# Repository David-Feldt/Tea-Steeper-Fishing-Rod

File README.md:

# Tea steeping robot

I found myself forggetting to take my tea bag and how long its been in the water. This robot you set a timer and it will remove the tea bag to your desired time.
- Built using esp8266 devboard and esp8266 (based on freeRTOS)
- PCB was made in KiCad
- Mechanical is built with scrap material

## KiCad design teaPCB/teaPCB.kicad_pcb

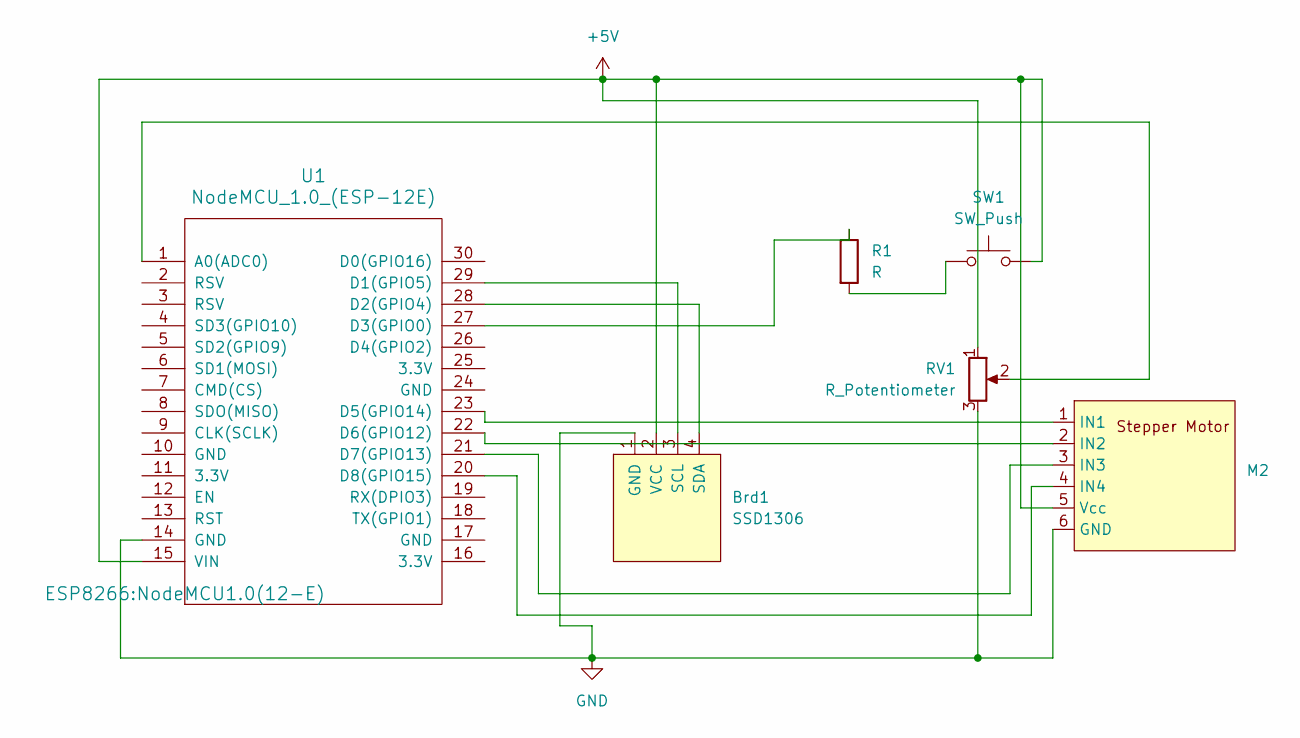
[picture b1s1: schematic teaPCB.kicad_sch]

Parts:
Brd1: SSD1306; 128x64OLED
M2: stepper motor
R1: R; R_Axial_DIN0207_L6.3mm_D2.5mm_P10.16mm_Horizontal
RV1: R_Potentiometer; Potentiometer_Alps_RK09Y11_Single_Horizontal
SW1: SW_Push; SW_Push_2P1T_Toggle_CK_PVA1xxH1xxxxxxV2
U1: NodeMCU_1.0_(ESP-12E); NodeMCU1.0(12-E)

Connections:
+5V: Brd1.2 (VCC), M2.5 (Vcc), RV1.1, SW1.2, U1.15 (VIN)
GND: Brd1.1 (GND), M2.6 (GND), RV1.3, U1.14 (GND)
unnamed: Brd1.3 (SCL), U1.29 (D1(GPIO5))
unnamed: Brd1.4 (SDA), U1.28 (D2(GPIO4))
unnamed: M2.1 (IN1), U1.23 (D5(GPIO14))
unnamed: M2.2 (IN2), U1.22 (D6(GPIO12))
unnamed: M2.3 (IN3), U1.21 (D7(GPIO13))
unnamed: M2.4 (IN4), U1.20 (D8(GPIO15))
unnamed: R1.2, SW1.1
unnamed: RV1.2, U1.1 (A0(ADC0))
unnamed: R1.1, U1.27 (D3(GPIO0))

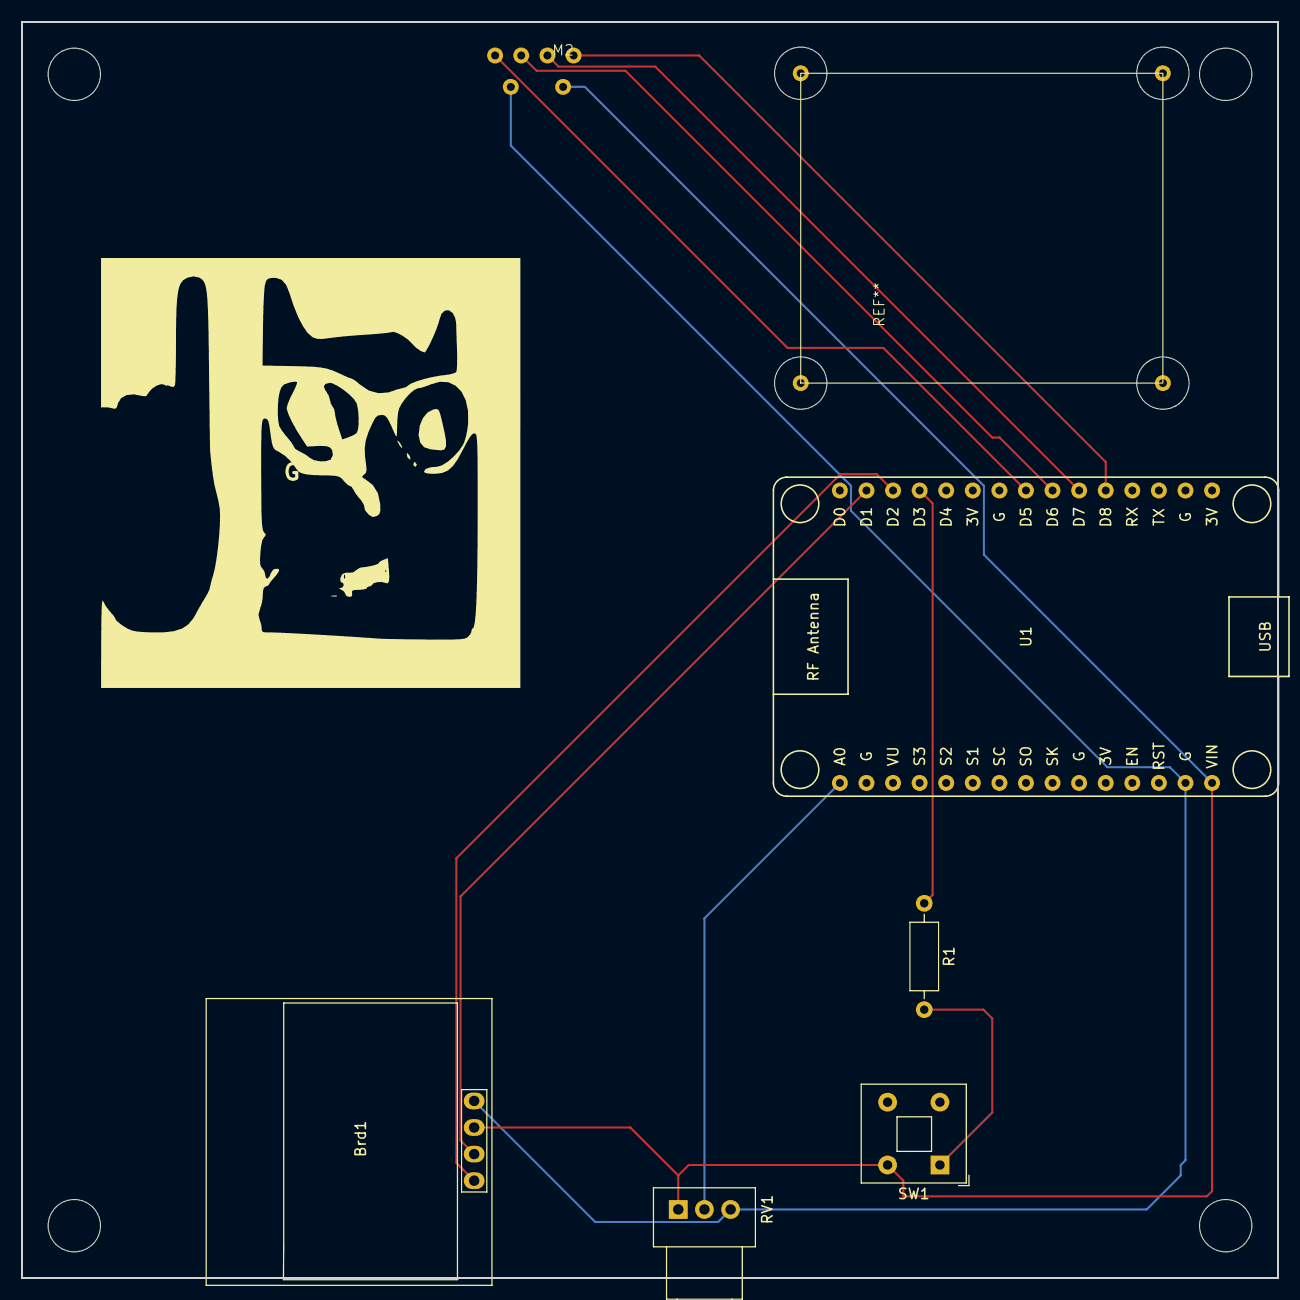
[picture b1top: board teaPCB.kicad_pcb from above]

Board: 2 copper layers, 120.0 x 120.0 mm, 6 parts (0 on the bottom side), 11 nets.

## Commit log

2024-09-19 push button code & potentiometer
2024-09-19 remove build?
2024-10-04 major changes almost working
